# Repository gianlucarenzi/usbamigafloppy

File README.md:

USB floppy controller for Amiga disks
=====================================

This is a USB floppy disk controller, for reading and writing amiga ADF disks. In
conjunction with the ArduinoFloppyDiskReader. The .zip file containing the executable
usable in Windows OS can be downloaded from:

https://github.com/gianlucarenzi/ArduinoFloppyDiskReader/blob/master/ArduinoFloppyReader/ArduinoFloppyReaderWin/res/ADFReaderWriter22.zip

It allows archiving amiga disks as ADF disk images, or writing ADF disk images back to disks, to use
with an Amiga computer (real or emulated).

The firmware for this controller is based on the same project by Rob Smith (https://github.com/RobSmithDev/ArduinoFloppyDiskReader),
converted to run on standalone AVR hardware (as opposed to an arduino) by John
Tsiombikas, and slightly adapted for my new hardware project.

The new AVR hardware is designed to be compatible with the original host
software, so you may use the `AmigaFloppyReader` or `AmigaFloppyReaderWin`
programs from Rob's project, if you prefer.

Directory structure:

  * `hw` - hardware: kicad files and pdf schematics.
  * `fw` - firmware for the AVR microcontroller and FTDI chips
  * `amigafloppy` - host program for reading/writing ADF images.

Note: The `amigafloppy` host program is not completed yet. And it's not a high
priority, since Rob's original .NET programs seem to work fine with wine on
GNU/Linux. I'd like to complete it at some stage, but I can't say when that will
happen. Contributions are of course welcome, but please coordinate with me
first. Until then, please use `AmigaFloppyReader` or `AmigaFloppyReaderWin`.

Rendered Images
===============
# Front
# Back
# Overall

Hardware License
================
Copyright (C) 2018/2021 Gianluca Renzi <gianlucarenzi@eurek.it> <icjtqr@gmail.com>

Original work Copyright (C) 2018 John Tsiombikas <nuclear@member.fsf.org>

The hardware of this project is released as free/open hardware under the
Creative Commons Attribution Share-Alike license. See `LICENSE.hw` for details.

Firmware License
================
Copyright (C) 2017 Rob Smith <rob@robsmithdev.co.uk>

Copyright (C) 2018 John Tsiombikas <nuclear@member.fsf.org>

Copyright (C) 2018/2021 Gianluca Renzi <icjtqr@gmail.com>

The microcontroller firmware of this project is released as free software,
under the terms of the GNU General Public License v3, or later.  See
`LICENSE.sw` for details.

Software License
================
Copyright (C) 2018 John Tsiombikas <nuclear@member.fsf.org>

The host software (amigafloppy tool) is released as free software, under the
terms of the GNU General Public License v3, or later. See `LICENSE.sw` or licence.txt for
details.

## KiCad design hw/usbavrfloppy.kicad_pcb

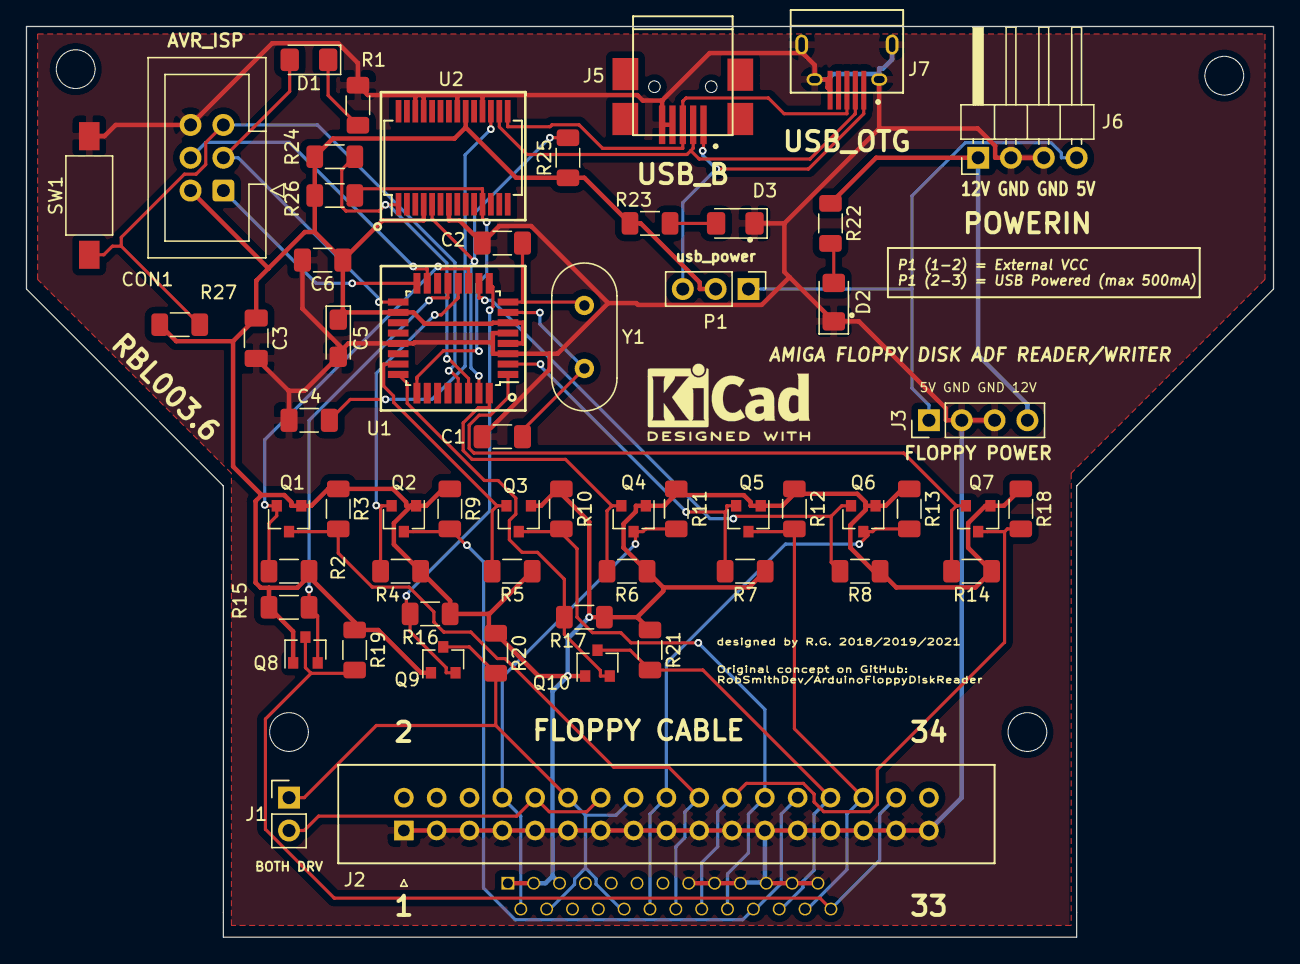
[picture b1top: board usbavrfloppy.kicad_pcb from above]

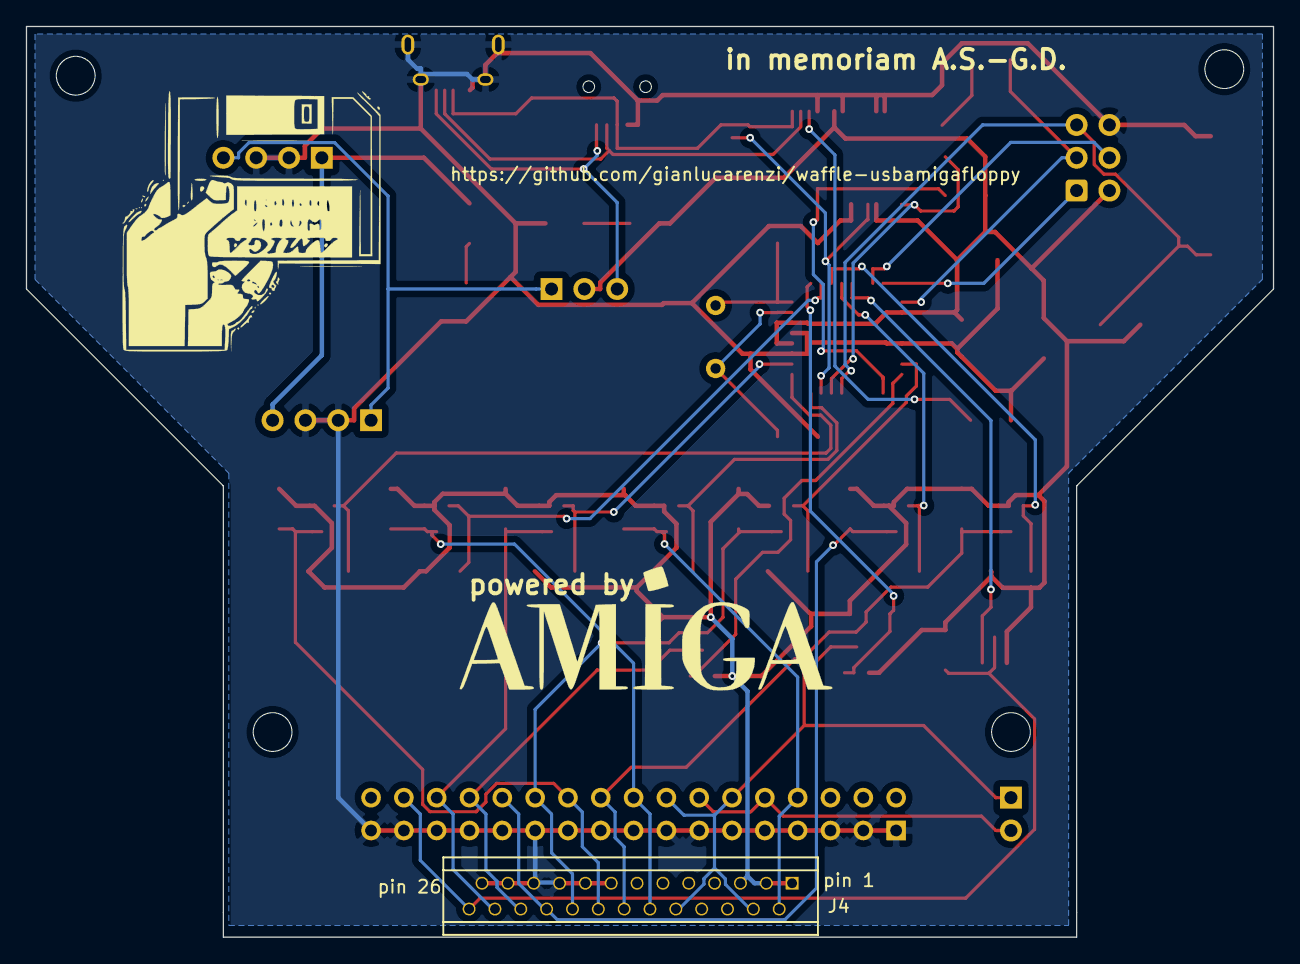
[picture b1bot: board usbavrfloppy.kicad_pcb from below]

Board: 2 copper layers, 96.5 x 70.5 mm, 66 parts (3 on the bottom side), 41 nets.

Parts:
AMIGALOGO: LOGO; amigaLogo_BW_31x12mm
C1, C2: 22pF; C_1206_3216Metric_Pad1.33x1.80mm_HandSolder
C3, C4, C6: 100nF; C_1206_3216Metric_Pad1.33x1.80mm_HandSolder
C5: 2.2uF; CP_EIA-3216-18_Kemet-A_Pad1.58x1.35mm_HandSolder
CON1: Conn_02x03; IDC-Header_2x03_P2.54mm_Vertical
D1: ACT; LED_1206_3216Metric_Pad1.42x1.75mm_HandSolder
D2, D3: Led_Small; LED_1206_3216Metric_Pad1.42x1.75mm_HandSolder
J1: bothdrv; PinHeader_1x02_P2.54mm_Vertical
J2: floppy_conn; IDC-Header_2x17_P2.54mm_Vertical_Lock
J3: floppy_power; PinHeader_1x04_P2.54mm_Vertical
J4: FPC Floppy; HLW26R-6C7LF
J5: USB_B; USB_Mini-B_Large_Pads
J6: PWRIN; PinHeader_1x04_P2.54mm_Horizontal
J7: USB_OTG; USB_Micro-B_Large_Pads
LOGO: KiCad-Logo2_5mm_SilkScreen
P1: CONN_01X03; PinHeader_1x03_P2.54mm_Vertical
P2, P3, P4, P5: CONN_01X01; MountingHole_3mm
Q1, Q2, Q3, Q4, Q5, Q6, Q7, Q8, Q9, Q10: BSS138; SOT-23
R1, R23: 330; R_1206_3216Metric_Pad1.30x1.75mm_HandSolder
R2, R3, R4, R5, R6, R7, R8, R9, R10, R11, R12, R13, R14, R15, R16, R17, R18, R19, R20, R21, R24, R25, R26: 10k; R_1206_3216Metric_Pad1.30x1.75mm_HandSolder
R22: 1k; R_1206_3216Metric_Pad1.30x1.75mm_HandSolder
R27: 4.7k; R_1206_3216Metric_Pad1.30x1.75mm_HandSolder
SW1: ~mRESET; SW_SPST_FSMSM_3D
U1: ATmega88PA-AU; TQFP-32_7x7mm_P0.8mm
U2: FT232RL; SSOP-28_5.3x10.2mm_P0.65mm
WBLOGO: LOGO; amigaWorkBench1
Y1: 16MHz; Crystal_HC49-4H_Vertical

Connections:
+12V: J3.4, J6.1, R22.1
/CTS: R26.2, U1.25, U2.11
/MISO: CON1.1, U1.16
/MOSI: CON1.4, U1.15
/RXD: R24.2, U1.30, U2.1
/SCK: CON1.3, D1.2, U1.17
/TXD: R25.2, U1.31, U2.5
/USBD+: J5.3, J7.3, U2.15
/USBD-: J5.2, J7.2, U2.16
/~DIR: J2.18, J4.12, Q6.3, R13.2
/~INDEX: J2.8, J4.2, Q4.3, R11.2
/~MOTEB: J1.1, J2.12, J2.16, J4.4, J4.10, Q9.3, R20.2
/~RDATA: J2.30, J4.24, Q5.3, R12.2
/~SIDE1: J2.32, J4.26, Q8.3, R19.2
/~STEP: J2.20, J4.14, Q1.3, R3.2
/~TRK0: J2.26, J4.20, Q2.3, R9.2
/~WDATA: J2.22, J4.16, Q7.3, R18.2
/~WGATE: J2.24, J4.18, Q3.3, R10.2
/~WPROT: J2.28, J4.22, Q10.3, R21.2
/~mDIR: Q6.2, R8.2, U1.10
/~mHSEL: Q8.2, R15.2, U1.13
/~mINDEX: Q4.2, R6.2, U1.32
/~mMOTEN: Q9.2, R16.2, U1.9
/~mRDATA: Q5.2, R7.2, U1.2
/~mRESET: CON1.5, R27.1, SW1.1, U1.29
/~mSTEP: Q1.2, R2.2, U1.11
/~mTRK0: Q2.2, R4.2, U1.12
/~mWDATA: Q7.2, R14.2, U1.1
/~mWGATE: Q3.2, R5.2, U1.23
/~mWPROTECT: Q10.2, R17.2, U1.24
GND: C1.1, C2.1, C3.2, C4.1, C5.2, C6.2, CON1.6, D2.1, D3.1, J2.1, J2.3, J2.5, J2.7, J2.9, J2.11, J2.13, J2.15, J2.17, J2.19, J2.21, J2.23, J2.25, J2.27, J2.29, J2.31, J2.33, J3.2, J3.3, J4.15, J4.17, J4.19, J4.21, J4.23, J4.25, J5.4, J5.5, J6.2, J6.3, J7.5, J7.6, R1.2, SW1.2, U1.3, U1.5, U1.21, U2.7, U2.18, U2.21, U2.25, U2.26
unnamed: C1.2, U1.7, Y1.2
unnamed: C2.2, U1.8, Y1.1
unnamed: C4.2, U2.17
unnamed: D1.1, R1.1
unnamed: D2.2, R22.2
unnamed: D3.2, R23.2
unnamed: J1.2, J2.10, J2.14
VCC: J3.1, J6.4, P1.1
VCC_USB: J5.1, J7.1, P1.3
Vcc_FLOPPY: C3.1, C5.1, C6.1, CON1.2, J4.1, J4.3, J4.5, P1.2, Q1.1, Q2.1, Q3.1, Q4.1, Q5.1, Q6.1, Q7.1, Q8.1, Q9.1, Q10.1, R2.1, R3.1, R4.1, R5.1, R6.1, R7.1, R8.1, R9.1, R10.1, R11.1, R12.1, R13.1, R14.1, R15.1, R16.1, R17.1, R18.1, R19.1, R20.1, R21.1, R23.1, R24.1, R25.1, R26.1, R27.2, U1.4, U1.6, U1.18, U2.4, U2.20

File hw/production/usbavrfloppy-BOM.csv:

"Id";"Designator";"Package";"Quantity";"Designation";"Supplier and ref";
1;"AMIGALOGO";"amigaLogo_BW_31x12mm";1;"LOGO";;;
2;"WBLOGO";"amigaWorkBench1";1;"LOGO";;;
3;"LOGO";"KiCad-Logo2_5mm_SilkScreen";1;"KiCad-Logo2_5mm_SilkScreen";;;
4;"CON1";"IDC-Header_2x03_P2.54mm_Vertical";1;"Conn_02x03";;;
5;"SW1";"SW_SPST_FSMSM_3D";1;"~mRESET";;;
6;"J5";"USB_Mini-B_Large_Pads";1;"USB_B";;;
7;"J7";"USB_Micro-B_Large_Pads";1;"USB_OTG";;;
8;"C1,C2";"C_1206_3216Metric_Pad1.33x1.80mm_HandSolder";2;"22pF";;;
9;"C3,C4,C6";"C_1206_3216Metric_Pad1.33x1.80mm_HandSolder";3;"100nF";;;
10;"C5";"CP_EIA-3216-18_Kemet-A_Pad1.58x1.35mm_HandSolder";1;"2.2uF";;;
11;"D1";"LED_1206_3216Metric_Pad1.42x1.75mm_HandSolder";1;"ACT";;;
12;"D2,D3";"LED_1206_3216Metric_Pad1.42x1.75mm_HandSolder";2;"Led_Small";;;
13;"J1";"PinHeader_1x02_P2.54mm_Vertical";1;"bothdrv";;;
14;"J2";"IDC-Header_2x17_P2.54mm_Vertical_Lock";1;"floppy_conn";;;
15;"J3";"PinHeader_1x04_P2.54mm_Vertical";1;"floppy_power";;;
16;"J4";"HLW26R-6C7LF";1;"FPC Floppy";;;
17;"J6";"PinHeader_1x04_P2.54mm_Horizontal";1;"PWRIN";;;
18;"P1";"PinHeader_1x03_P2.54mm_Vertical";1;"CONN_01X03";;;
19;"P2,P3,P4,P5";"MountingHole_3mm";4;"CONN_01X01";;;
20;"Q1,Q2,Q3,Q4,Q5,Q6,Q7,Q8,Q9,Q10";"SOT-23";10;"BSS138";;;
21;"R1,R23";"R_1206_3216Metric_Pad1.30x1.75mm_HandSolder";2;"330";;;
22;"R2,R3,R4,R5,R6,R7,R8,R9,R10,R11,R12,R13,R14,R15,R16,R17,R18,R19,R20,R21,R24,R25,R26";"R_1206_3216Metric_Pad1.30x1.75mm_HandSolder";23;"10k";;;
23;"R22";"R_1206_3216Metric_Pad1.30x1.75mm_HandSolder";1;"1k";;;
24;"R27";"R_1206_3216Metric_Pad1.30x1.75mm_HandSolder";1;"4.7k";;;
25;"U1";"TQFP-32_7x7mm_P0.8mm";1;"ATmega88PA-AU";;;
26;"U2";"SSOP-28_5.3x10.2mm_P0.65mm";1;"FT232RL";;;
27;"Y1";"Crystal_HC49-4H_Vertical";1;"16MHz";;;

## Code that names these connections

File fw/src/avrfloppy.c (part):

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#include <string.h>
#include <stdio.h>

#define INDEX_PORT			PIND
#define INDEX_BIT			0x04

#define WDATA_PORT			PORTD
#define WDATA_BIT			0x08

#define RDATA_PORT			PIND
#define RDATA_BIT			0x10

#define MOTOR_PORT			PORTD
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#define HEADSEL_PORT		PORTB
#define HEAD_SELECT_BIT		0x02

#define WGATE_PORT			PORTC
#define WGATE_BIT			0x01

#define WPROT_PORT			PINC
#define WPROT_BIT			0x02

#define CTS_PORT			PORTC
#define CTS_BIT				0x04

#define LED_PORT			PORTB
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	DDRD = 0xe8;	/* outputs: 3 (write), 5 (motor en), 6 (dir), 7 (step) */

	/* Do these right away to prevent the disk being written to */
	PORTC = WGATE_BIT | WPROT_BIT;	/* write gate off and pullup on pin 1 (wprot) */
	PORTD = WDATA_BIT | RDATA_BIT;	/* write data hight and pullup on pin 4 (read) */
	PORTB = TRACK0_BIT;				/* pullup on track0 detect */

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		 */
		for(j=0; j<20; j++) {
			for(i=0; i<60000; i++) {
				if(INDEX_PORT & INDEX_BIT) state1 = 1; else state2 = 1;
				if(state1 && state2) break;
			}
			if (state1 && state2) break;
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
		for(j=0; j<20; j++) {
			for(i=0; i<60000; i++) {
				if(RDATA_PORT & RDATA_BIT) state1 = 1; else state2 = 1;
				if(state1 && state2) break;
			}
			if (state1 && state2) break;
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	/* Enable writing */
	WGATE_PORT &= ~WGATE_BIT;

	/* While the INDEX pin is high wait.  Might as well write from the start of the track */
	if(wait_for_index)
		while(INDEX_PORT & INDEX_BIT) {};

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	/* Enable writing */
	WGATE_PORT &= ~WGATE_BIT;

	/* While the INDEX pin is high wait.  Might as well write from the start of the track */
	if(wait_for_index)
		while(INDEX_PORT & INDEX_BIT) {};

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	/* Signal we're active */
	LED_PORT |= LED_BIT;

	/* While the INDEX pin is high wait if the other end requires us to */
	if(read_byte_from_uart()) while(INDEX_PORT & INDEX_BIT);

	/* Prepare the two counter values as follows: */
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	/* Signal we're active */
	LED_PORT |= LED_BIT;

	/* While the INDEX pin is high wait if the other end requires us to */
	if(read_byte_from_uart()) while(INDEX_PORT & INDEX_BIT);

	/* Prepare the two counter values as follows: */
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	// Signal we're active
	LED_PORT |= LED_BIT;

	// While the INDEX pin is high wait 
	while(INDEX_PORT & INDEX_BIT) {};

	// Prepare the two counter values as follows:
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
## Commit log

2018-12-21 From CVS sources
2018-12-21 Retry the read or write command if EINTR or EAGAIN, otherwise returns the correct value...
2018-12-21 - Added baudrate as option - flushing all data when initializing
2018-12-21 - Added baudrate
2018-12-21 - Better Comments - Version 1.6 - During startup an easter-egg on serial appears! ;-P
2018-12-21 - I am using a usbasp-clone as programmer - My ATMega88 is a PA version as here in Eurek Srl (http://www.eurek.it) we have a plenty of them.
2018-12-21 - Added (C)opyright notice and FTDI stuff
2018-12-22 Inserted New Design Files
2018-12-22 New objects
2018-12-22 Added the image section and rebuilt production files for new footprints
2018-12-22 Deleted
2018-12-23 Added link to the Windows archive .zip
2018-12-23 typo
2018-12-23 corrected with the github format
2018-12-23 Re-generated after libraries cleanup
2018-12-23 updated libraries
2018-12-23 Removed
2019-01-06 Added ser_flush at the very initial stage and some printf for debugging
2019-01-06 simplified read/write
2019-01-06 Removed the RetroBitLab.pretty Library & updated configuration project
2019-01-20 added all kicad libraries
2019-02-11 Added overall image
2019-02-11 Modified for new components
2019-02-11 Modified for new 3d components and logos
2019-02-14 Added images
2019-02-14 Added GPLv3
2019-02-14 Better reading
2019-02-21 added filled zone top
2019-02-26 Optimized for speed
    Maybe optimized for writing a sector
2019-02-27 Optimization as in sketch
2019-02-28 Added footprint for idc connector
2019-04-12 Added BOM. It needs to be adapted for Mouser/DigiKey/...
2019-04-12 Added to the project after change component package size
2019-04-12 Changed from 0603/0806 to 1208
2019-06-02 Corrected some silkscreen issues
2019-06-17 Changed backside (SilkScreen Back) logo and text
2019-06-17 Modified Silkscreen for a resistor
2020-11-24 Corrected behaviour with slow CTS change for other FTDI compatible chipset like CH340G and similar USB-to-Serial converters. Need to be tested.
2020-11-24 It does not work always. Old version.
2021-03-19 Updated to RobSmith v1.7 (Experimental HD support)
2021-03-22 First Kicad 5 import
2021-03-23 Added for new Kicad 5
2021-03-23 New from Kicad 5
2021-03-23 Modified for final Kicad 5
2021-03-23 Bill Of Material (autogen)
2021-03-23 Date update
2021-04-05 Sent to JLCPCB 5th April 2021
2021-05-06 Added some footprints(?)

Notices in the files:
fw/src/avrfloppy.c:
Copyright (C) 2019 Gianluca Renzi (icjtqr@gmail.com)
Copyright (C) 2017-2018 Robert Smith (@RobSmithDev)
